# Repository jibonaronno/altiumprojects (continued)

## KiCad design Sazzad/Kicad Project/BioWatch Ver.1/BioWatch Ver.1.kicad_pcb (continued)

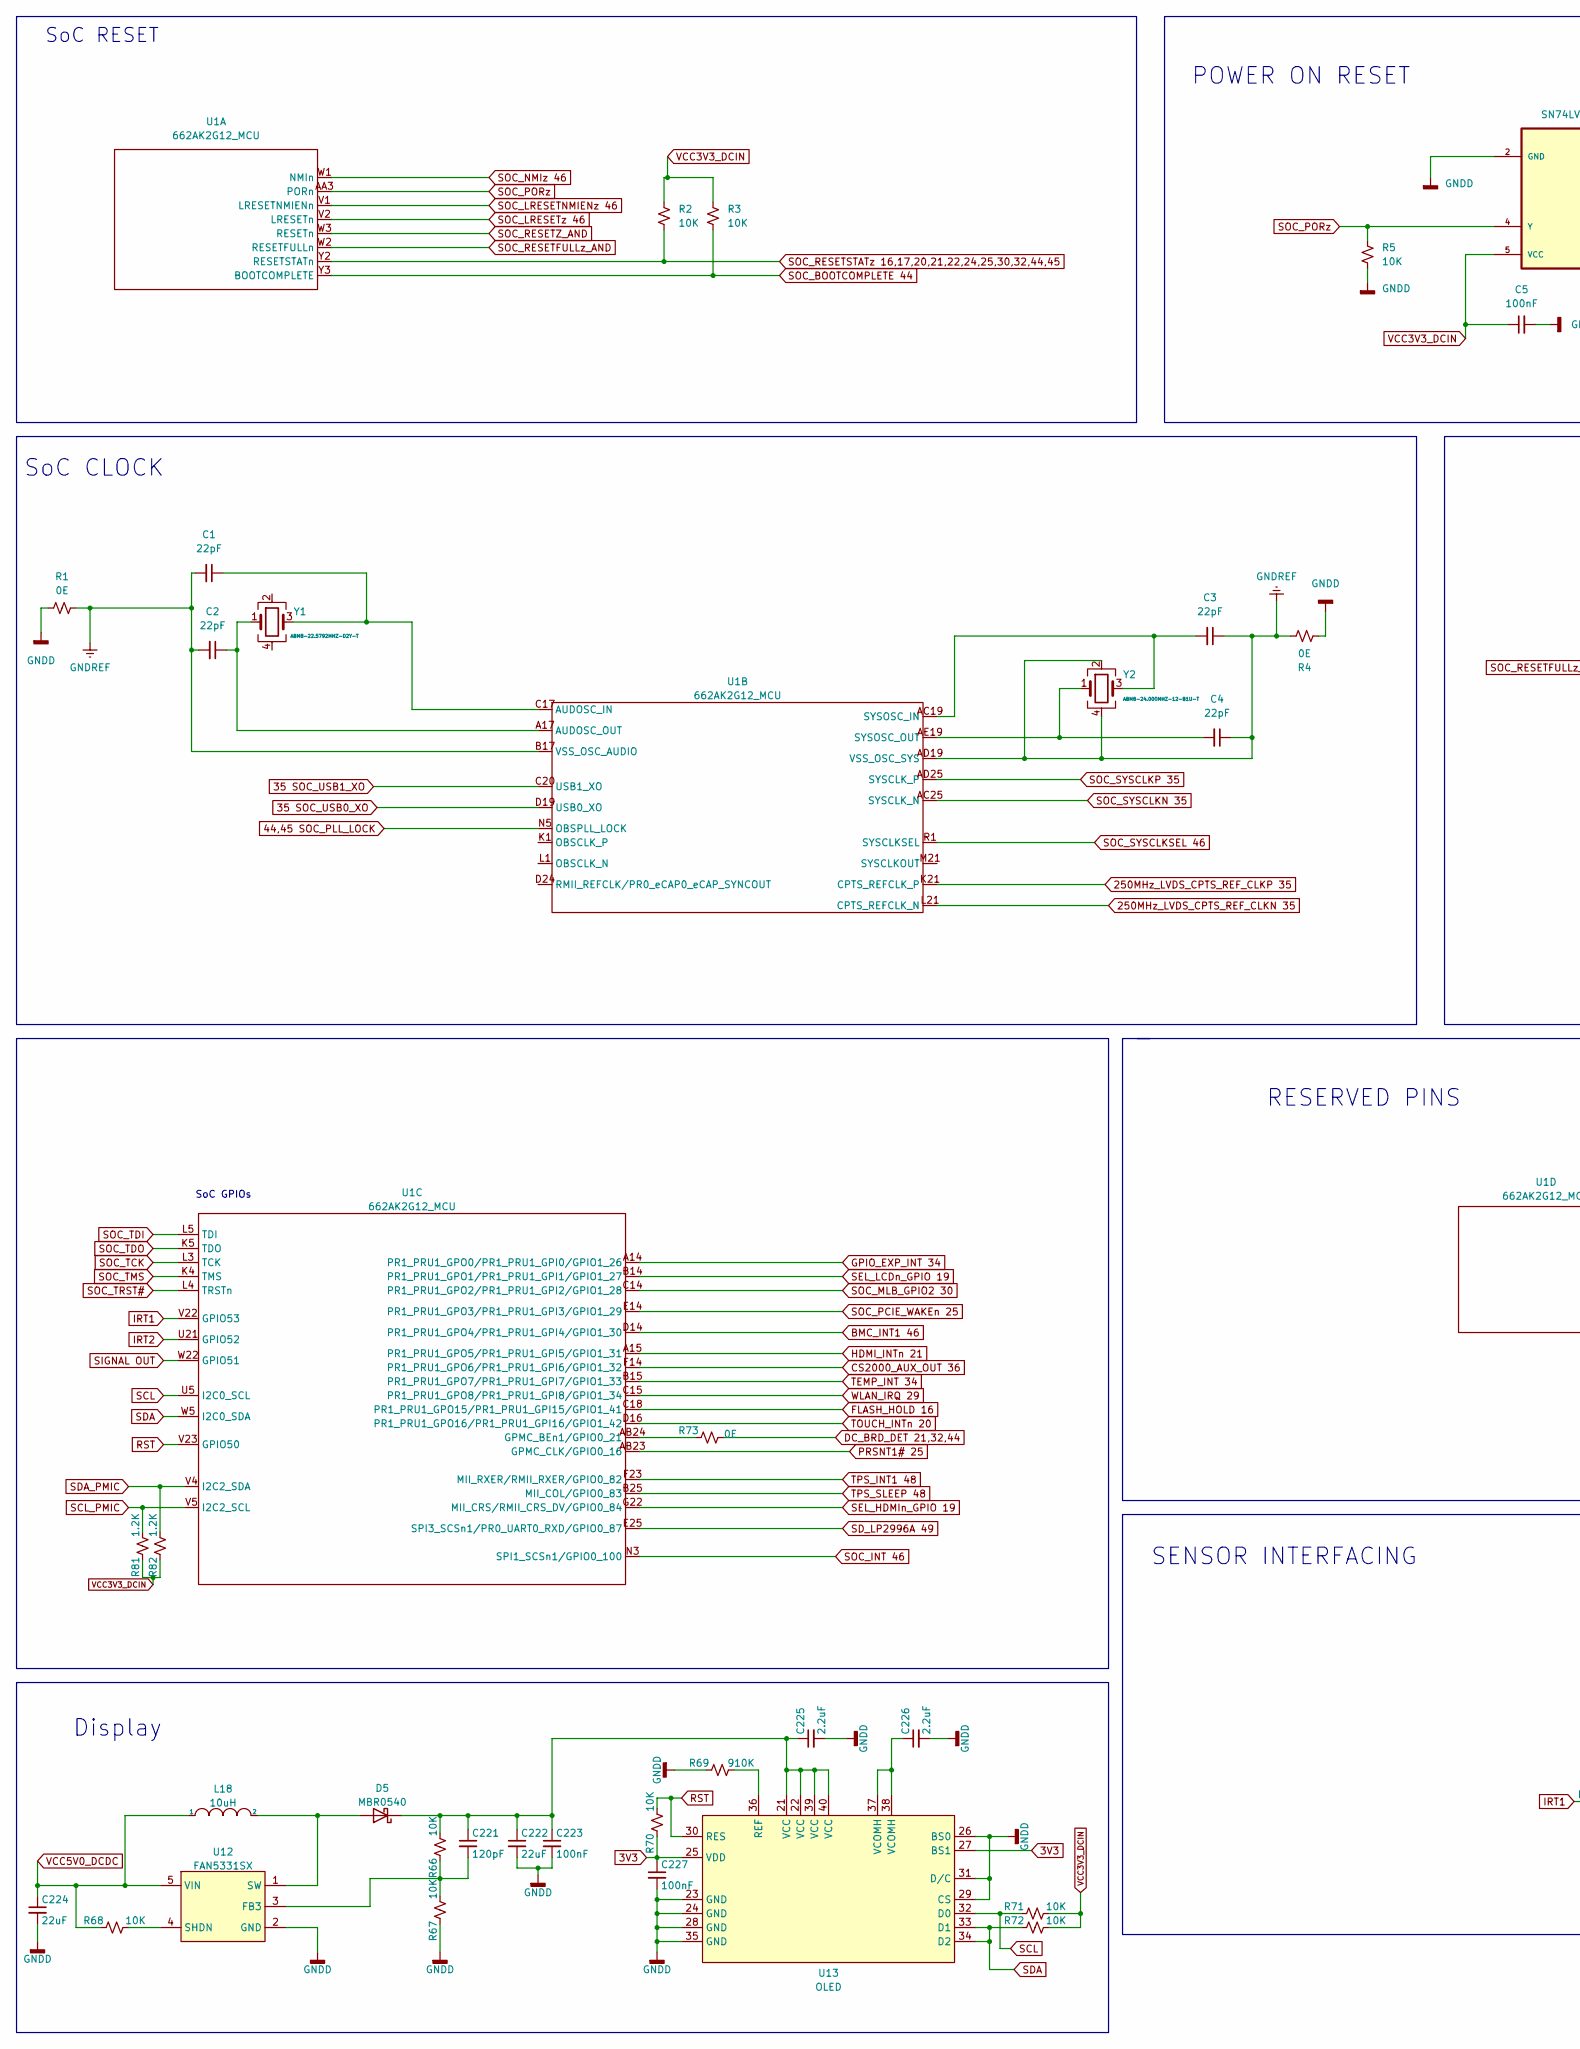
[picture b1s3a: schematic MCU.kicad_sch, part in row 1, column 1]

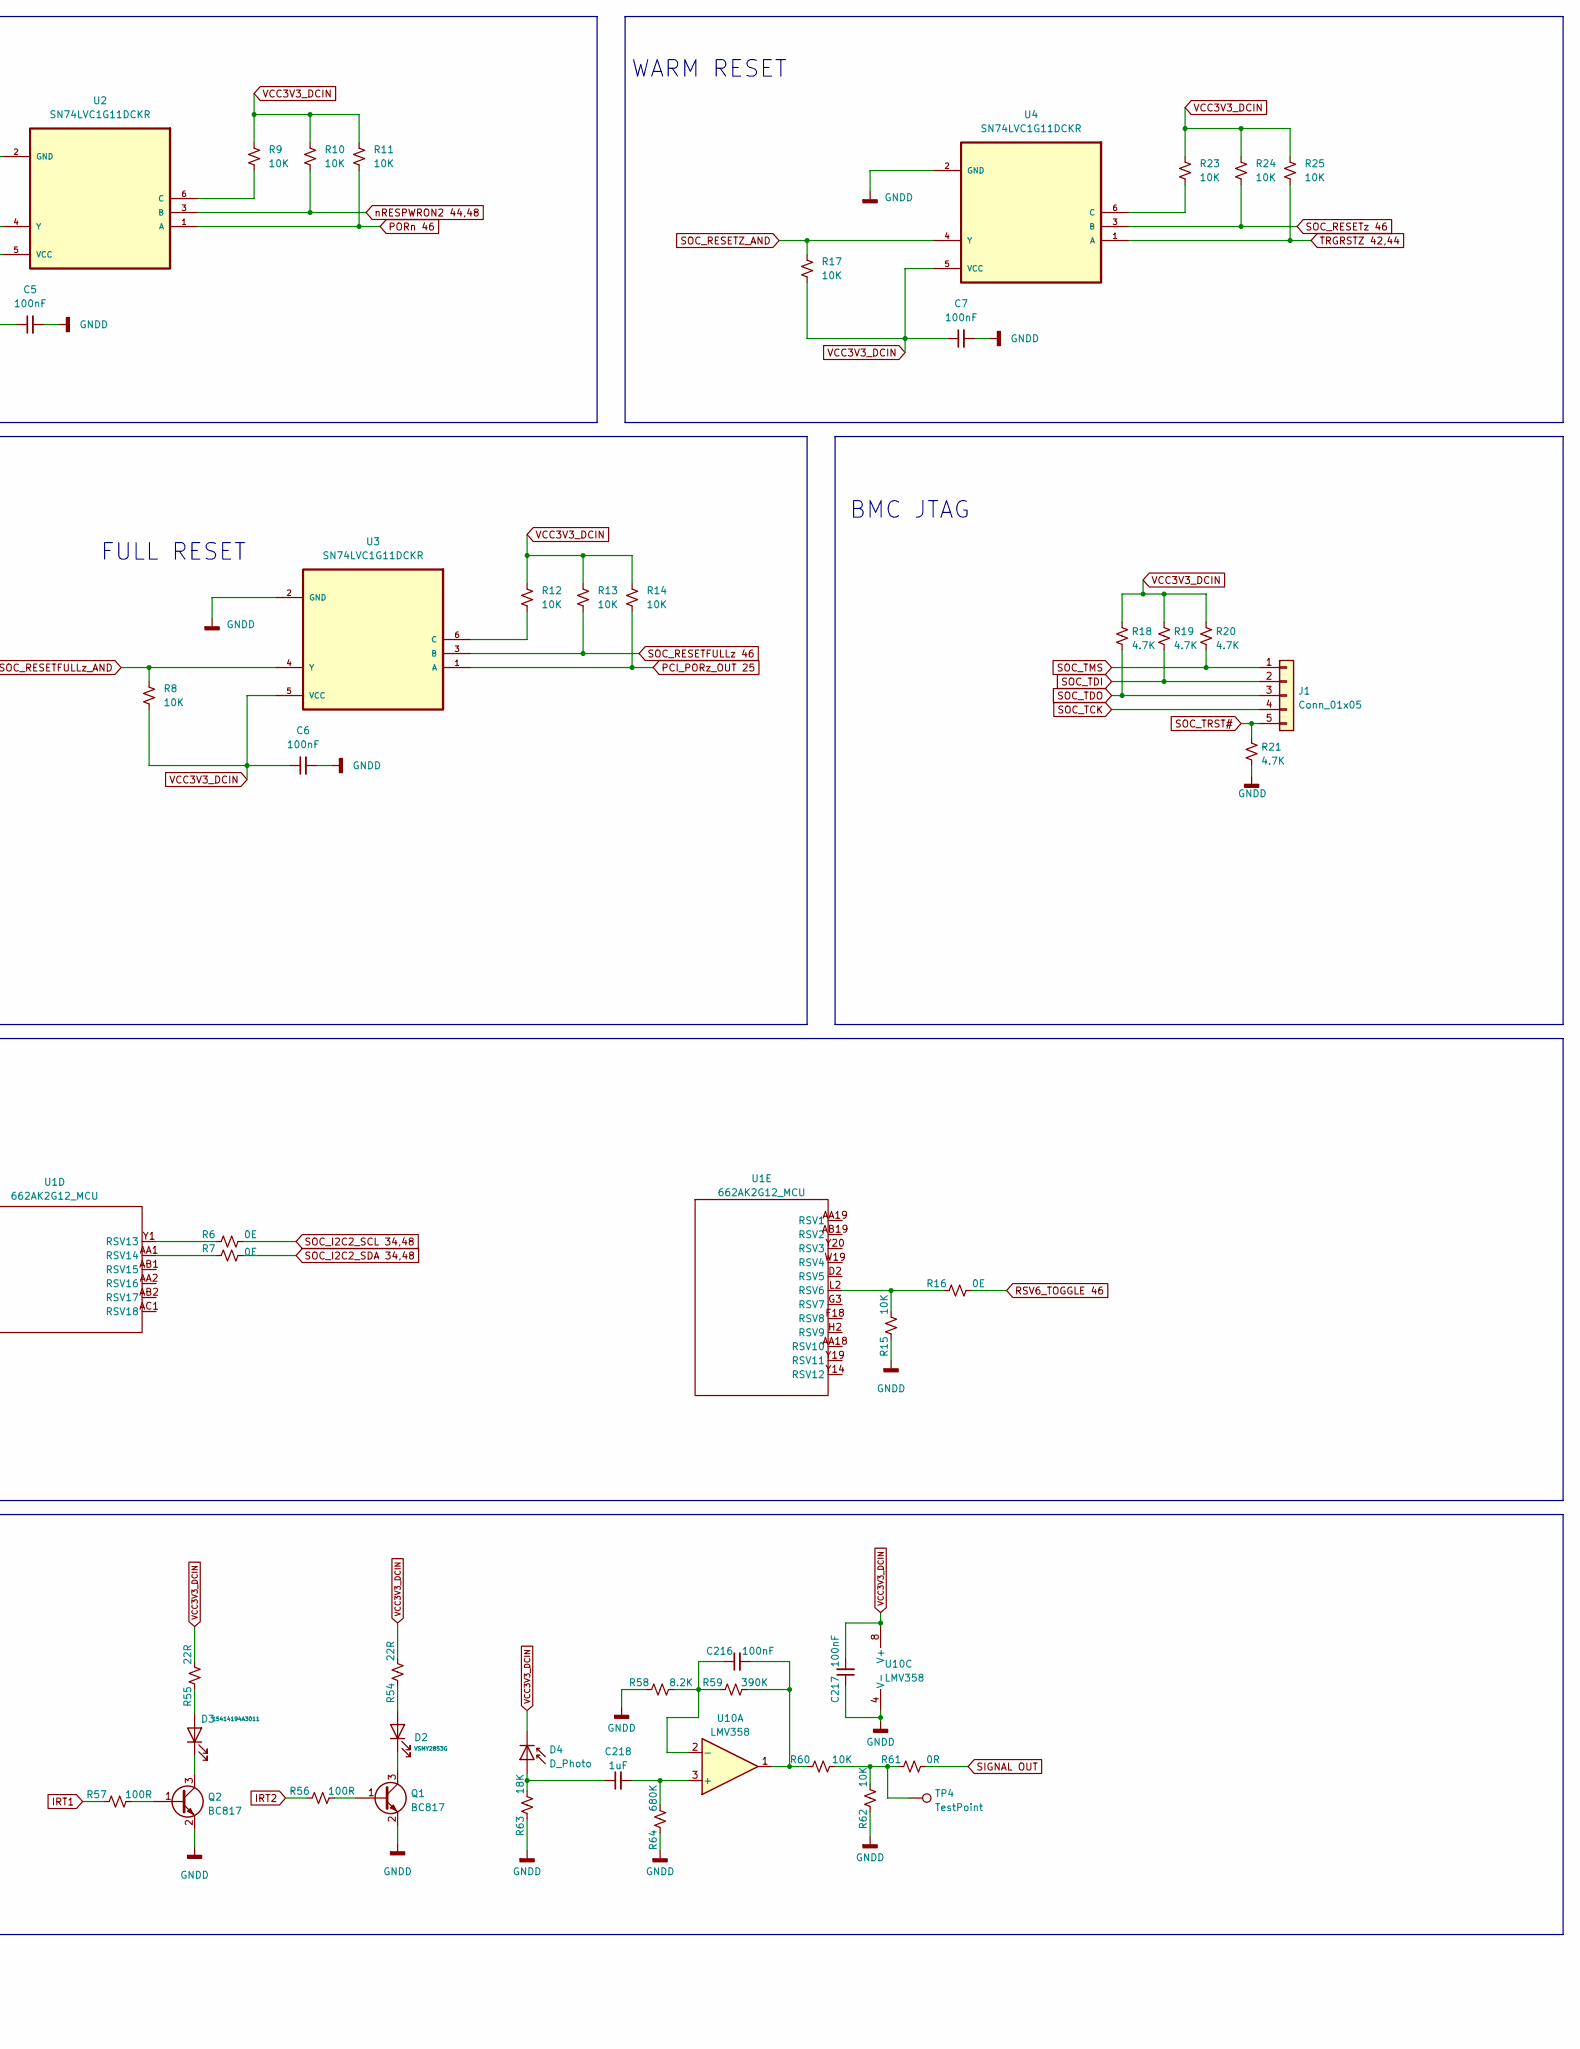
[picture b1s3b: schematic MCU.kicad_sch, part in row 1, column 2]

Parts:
C1, C2, C3, C4: 22pF; C_0402_1005Metric
C5, C6, C7, C216, C217, C223, C227: 100nF; C_0402_1005Metric
C218: 1uF; C_0402_1005Metric
C221: 120pF; C_0402_1005Metric
C222, C224: 22uF; C_0805_2012Metric
C225, C226: 2.2uF; C_0603_1608Metric
D2: VSMY2853G; LED_1812_4532Metric_Pad1.30x3.40mm_HandSolder
D3: 15414194A3011; LED_RGB_Wuerth-PLCC4_3.2x2.8mm_150141M173100
D4: D_Photo; LED_1812_4532Metric_Pad1.30x3.40mm_HandSolder
D5: MBR0540; D_SOD-123
J1: Conn_01x05; PinHeader_1x05_P2.54mm_Vertical
L18: 10uH; L_6.3x6.3_H3
Q1, Q2: BC817; SOT-23
R1, R4: 0E; R_0402_1005Metric
R2, R3, R5, R8, R9, R10, R11, R12, R13, R14, R15, R17, R23, R24, R25, R60, R62, R66, R67, R68, R70, R71, R72: 10K; R_0603_1608Metric
R6, R7, R16, R73: 0E; R_0603_1608Metric
R18, R19, R20, R21: 4.7K; R_0603_1608Metric
R54, R55: 22R; R_0805_2012Metric
R56, R57: 100R; R_0603_1608Metric
R58: 8.2K; R_0603_1608Metric
R59: 390K; R_0603_1608Metric
R61: 0R; R_0603_1608Metric
R63: 18K; R_0603_1608Metric
R64: 680K; R_0603_1608Metric
R69: 910K; R_0603_1608Metric
R81, R82: 1.2K; R_0603_1608Metric
TP4: TestPoint; TestPoint_Pad_D1.0mm
U1: 662AK2G12_MCU; BGA625
U2, U3, U4: SN74LVC1G11DCKR; SOT-23-6_Handsoldering
U10: LMV358; SOIC-8-1EP_3.9x4.9mm_P1.27mm_EP2.29x3mm
U12: FAN5331SX; SOT-23-5_HandSoldering
U13: OLED; PinSocket_2x07_P2.54mm_Vertical
Y1: ABM8-22.5792MHZ-D2Y-T; Crystal_SMD_3225-4Pin_3.2x2.5mm_HandSoldering
Y2: ABM8-24.000MHZ-12-B1U-T; Crystal_SMD_3225-4Pin_3.2x2.5mm_HandSoldering

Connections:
3V3: C227.1, R70.1, U13.25 (VDD), U13.27 (BS1)
35 SOC_USB0_XO: U1.D19 (USB0_XO)
35 SOC_USB1_XO: U1.C20 (USB1_XO)
44,45 SOC_PLL_LOCK: U1.N5 (OBSPLL_LOCK)
250MHz_LVDS_CPTS_REF_CLKN 35: U1.L21 (CPTS_REFCLK_N)
250MHz_LVDS_CPTS_REF_CLKP 35: U1.K21 (CPTS_REFCLK_P)
BMC_INT1 46: U1.D14 (PR1_PRU1_GPO4/PR1_PRU1_GPI4/GPIO1_30)
CS2000_AUX_OUT 36: U1.F14 (PR1_PRU1_GPO6/PR1_PRU1_GPI6/GPIO1_32)
DC_BRD_DET 21,32,44: R73.2
FLASH_HOLD 16: U1.C18 (PR1_PRU1_GPO15/PR1_PRU1_GPI15/GPIO1_41)
GND: C5.2, C6.2, C7.2, C217.1, C222.2, C223.2, C224.2, C225.2, C226.2, C227.2, Q1.2 (E), Q2.2 (E), R1.2, R4.2, R5.2, R15.1, R21.2, R58.1, R62.1, R63.1, R64.1, R67.1, R69.1, U2.2 (GND), U3.2 (GND), U4.2 (GND), U10.4 (V-), U12.2 (GND), U13.23 (GND), U13.24 (GND), U13.26 (BS0), U13.28 (GND), U13.29 (CS), U13.31 (D/C), U13.35 (GND); also elsewhere on the board
GNDREF: C1.2, C2.2, C3.1, C4.1, R1.1, R4.1, U1.AD19 (VSS_OSC_SYS), U1.B17 (VSS_OSC_AUDIO), Y2.2, Y2.4
GPIO_EXP_INT 34: U1.A14 (PR1_PRU1_GPO0/PR1_PRU1_GPI0/GPIO1_26)
HDMI_INTn 21: U1.A15 (PR1_PRU1_GPO5/PR1_PRU1_GPI5/GPIO1_31)
IRT1: R57.1, U1.V22 (GPIO53)
IRT2: R56.1, U1.U21 (GPIO52)
unnamed: C1.1, U1.C17 (AUDOSC_IN), Y1.3
unnamed: C2.1, U1.A17 (AUDOSC_OUT), Y1.1
unnamed: C3.2, U1.AC19 (SYSOSC_IN), Y2.3
unnamed: C4.2, U1.AE19 (SYSOSC_OUT), Y2.1
unnamed: C216.1, R58.2, R59.1, U10.2 (-)
unnamed: C216.2, R59.2, R60.1, U10.1
unnamed: C218.1, D4.2 (A), R63.2
unnamed: C218.2, R64.2, U10.3 (+)
unnamed: C221.1, C222.1, C223.1, C225.1, D5.1 (K), R66.2, U13.21 (VCC), U13.22 (VCC), U13.39 (VCC), U13.40 (VCC)
unnamed: C221.2, R66.1, R67.2, U12.3 (FB3)
unnamed: C226.1, U13.37 (VCOMH), U13.38 (VCOMH)
unnamed: D2.1 (K), Q1.3 (C)
unnamed: D2.2 (A), R54.1
unnamed: D3.1 (K), Q2.3 (C)
unnamed: D3.4 (A), R55.1
unnamed: D5.2 (A), L18.2, U12.1 (SW)
unnamed: Q1.1 (B), R56.2
unnamed: Q2.1 (B), R57.2
unnamed: R6.1, U1.Y1 (RSV13)
unnamed: R7.1, U1.AA1 (RSV14)
unnamed: R9.2, U2.6 (C)
unnamed: R12.2, U3.6 (C)
unnamed: R15.2, R16.1, U1.L2 (RSV6)
unnamed: R23.2, U4.6 (C)
unnamed: R60.2, R61.1, R62.2, TP4.1
unnamed: R68.2, U12.4 (SHDN)
unnamed: R69.2, U13.36 (REF)
unnamed: R73.1, U1.AB24 (GPMC_BEn1/GPIO0_21)
PCI_PORz_OUT 25: R14.2, U3.1 (A)
PORn 46: R11.2, U2.1 (A)
PRSNT1# 25: U1.AB23 (GPMC_CLK/GPIO0_16)
RST: R70.2, U1.V23 (GPIO50), U13.30 (RES)
RSV6_TOGGLE 46: R16.2
SCL: R71.1, U1.U5 (I2C0_SCL), U13.32 (D0)
SCL_PMIC: R81.2, U1.V5 (I2C2_SCL); also elsewhere on the board
SDA: R72.1, U1.W5 (I2C0_SDA), U13.33 (D1), U13.34 (D2)
SDA_PMIC: R82.2, U1.V4 (I2C2_SDA); also elsewhere on the board
SD_LP2996A 49: U1.E25 (SPI3_SCSn1/PR0_UART0_RXD/GPIO0_87)
SEL_HDMIn_GPIO 19: U1.G22 (MII_CRS/RMII_CRS_DV/GPIO0_84)
SEL_LCDn_GPIO 19: U1.B14 (PR1_PRU1_GPO1/PR1_PRU1_GPI1/GPIO1_27)
SIGNAL OUT: R61.2, U1.W22 (GPIO51)
SOC_BOOTCOMPLETE 44: R3.2, U1.Y3 (BOOTCOMPLETE)
SOC_I2C2_SCL 34,48: R6.2
SOC_I2C2_SDA 34,48: R7.2
SOC_INT 46: U1.N3 (SPI1_SCSn1/GPIO0_100)
SOC_LRESETNMIENz 46: U1.V1 (LRESETNMIENn)
SOC_LRESETz 46: U1.V2 (LRESETn)
SOC_MLB_GPIO2 30: U1.C14 (PR1_PRU1_GPO2/PR1_PRU1_GPI2/GPIO1_28)
SOC_NMIz 46: U1.W1 (NMIn)
SOC_PCIE_WAKEn 25: U1.E14 (PR1_PRU1_GPO3/PR1_PRU1_GPI3/GPIO1_29)
SOC_PORz: R5.1, U1.AA3 (PORn), U2.4 (Y)
SOC_RESETFULLz 46: R13.2, U3.3 (B)
SOC_RESETFULLz_AND: R8.1, U1.W2 (RESETFULLn), U3.4 (Y)
SOC_RESETSTATz 16,17,20,21,22,24,25,30,32,44,45: R2.2, U1.Y2 (RESETSTATn)
SOC_RESETZ_AND: R17.1, U1.W3 (RESETn), U4.4 (Y)
SOC_RESETz 46: R24.2, U4.3 (B)
SOC_SYSCLKN 35: U1.AC25 (SYSCLK_N)
SOC_SYSCLKSEL 46: U1.R1 (SYSCLKSEL)
SOC_TCK: J1.4, U1.L3 (TCK)
SOC_TDI: J1.2, R19.2, U1.L5 (TDI)
SOC_TDO: J1.3, R18.2, U1.K5 (TDO)
SOC_TMS: J1.1, R20.2, U1.K4 (TMS)
SOC_TRST#: J1.5, R21.1, U1.L4 (TRSTn)
TEMP_INT 34: U1.B15 (PR1_PRU1_GPO7/PR1_PRU1_GPI7/GPIO1_33)
TOUCH_INTn 20: U1.D16 (PR1_PRU1_GPO16/PR1_PRU1_GPI16/GPIO1_42)
TPS_INT1 48: U1.F23 (MII_RXER/RMII_RXER/GPIO0_82)
TPS_SLEEP 48: U1.B25 (MII_COL/GPIO0_83)
TRGRSTZ 42,44: R25.2, U4.1 (A)
VCC3V3_DCIN: C5.1, C6.1, C7.1, C217.2, D4.1 (K), R2.1, R3.1, R8.2, R9.1, R10.1, R11.1, R12.1, R13.1, R14.1, R17.2, R18.1, R19.1, R20.1, R23.1, R24.1, R25.1, R54.2, R55.2, R71.2, R72.2, R81.1, R82.1, U2.5 (VCC), U3.5 (VCC), U4.5 (VCC), U10.8 (V+); also elsewhere on the board
VCC5V0_DCDC: C224.1, L18.1, R68.1, U12.5 (VIN); also elsewhere on the board
WLAN_IRQ 29: U1.C15 (PR1_PRU1_GPO8/PR1_PRU1_GPI8/GPIO1_34)
nRESPWRON2 44,48: R10.2, U2.3 (B)

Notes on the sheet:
BMC JTAG
RESERVED PINS
POWER ON RESET
SoC RESET
FULL RESET
WARM RESET
SENSOR INTERFACING
SoC GPIOs
Display
SoC CLOCK

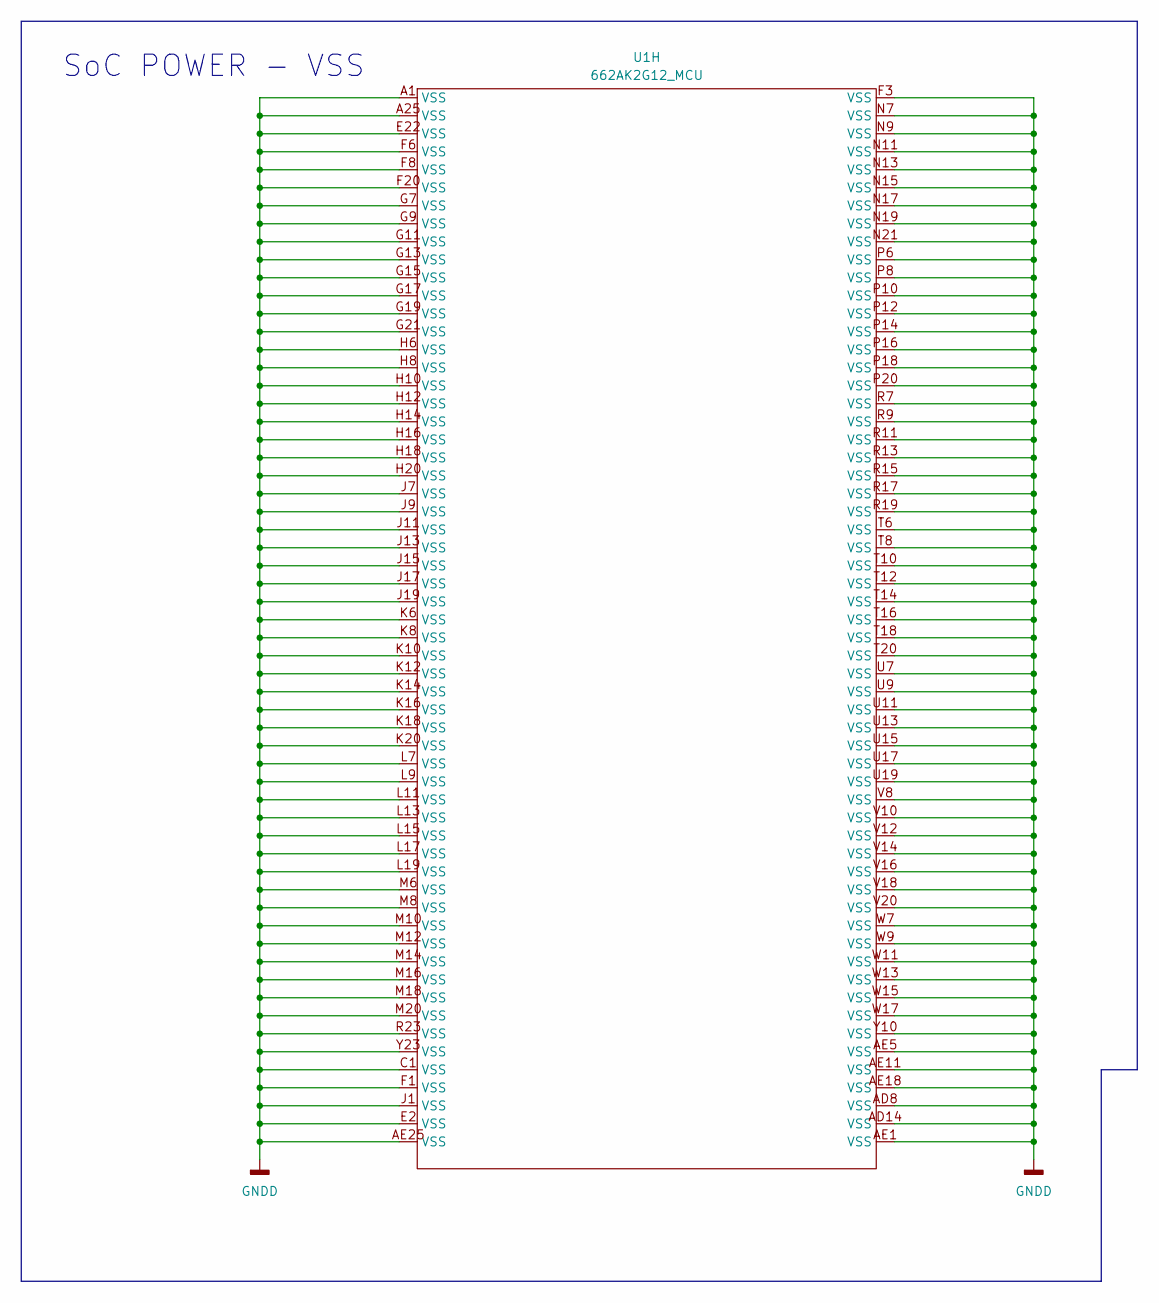
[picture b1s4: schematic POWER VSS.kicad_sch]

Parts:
U1: 662AK2G12_MCU; BGA625

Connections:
GND: U1.A1 (VSS), U1.A25 (VSS), U1.AD8 (VSS), U1.AD14 (VSS), U1.AE1 (VSS), U1.AE5 (VSS), U1.AE11 (VSS), U1.AE18 (VSS), U1.AE25 (VSS), U1.C1 (VSS), U1.E2 (VSS), U1.E22 (VSS), U1.F1 (VSS), U1.F3 (VSS), U1.F6 (VSS), U1.F8 (VSS), U1.F20 (VSS), U1.G7 (VSS), U1.G9 (VSS), U1.G11 (VSS), U1.G13 (VSS), U1.G15 (VSS), U1.G17 (VSS), U1.G19 (VSS), U1.G21 (VSS), U1.H6 (VSS), U1.H8 (VSS), U1.H10 (VSS), U1.H12 (VSS), U1.H14 (VSS), U1.H16 (VSS), U1.H18 (VSS), U1.H20 (VSS), U1.J1 (VSS), U1.J7 (VSS), U1.J9 (VSS), U1.J11 (VSS), U1.J13 (VSS), U1.J15 (VSS), U1.J17 (VSS), U1.J19 (VSS), U1.K6 (VSS), U1.K8 (VSS), U1.K10 (VSS), U1.K12 (VSS), U1.K14 (VSS), U1.K16 (VSS), U1.K18 (VSS), U1.K20 (VSS), U1.L7 (VSS), U1.L9 (VSS), U1.L11 (VSS), U1.L13 (VSS), U1.L15 (VSS), U1.L17 (VSS), U1.L19 (VSS), U1.M6 (VSS), U1.M8 (VSS), U1.M10 (VSS), U1.M12 (VSS), U1.M14 (VSS), U1.M16 (VSS), U1.M18 (VSS), U1.M20 (VSS), U1.N7 (VSS), U1.N9 (VSS), U1.N11 (VSS), U1.N13 (VSS), U1.N15 (VSS), U1.N17 (VSS), U1.N19 (VSS), U1.N21 (VSS), U1.P6 (VSS), U1.P8 (VSS), U1.P10 (VSS), U1.P12 (VSS), U1.P14 (VSS), U1.P16 (VSS), U1.P18 (VSS), U1.P20 (VSS), U1.R7 (VSS), U1.R9 (VSS), U1.R11 (VSS), U1.R13 (VSS), U1.R15 (VSS), U1.R17 (VSS), U1.R19 (VSS), U1.R23 (VSS), U1.T6 (VSS), U1.T8 (VSS), U1.T10 (VSS), U1.T12 (VSS), U1.T14 (VSS), U1.T16 (VSS), U1.T18 (VSS), U1.T20 (VSS), U1.U7 (VSS), U1.U9 (VSS), U1.U11 (VSS), U1.U13 (VSS), U1.U15 (VSS), U1.U17 (VSS), U1.U19 (VSS), U1.V8 (VSS), U1.V10 (VSS), U1.V12 (VSS), U1.V14 (VSS), U1.V16 (VSS), U1.V18 (VSS), U1.V20 (VSS), U1.W7 (VSS), U1.W9 (VSS), U1.W11 (VSS), U1.W13 (VSS), U1.W15 (VSS), U1.W17 (VSS), U1.Y10 (VSS), U1.Y23 (VSS); also elsewhere on the board

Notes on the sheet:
SoC POWER - VSS

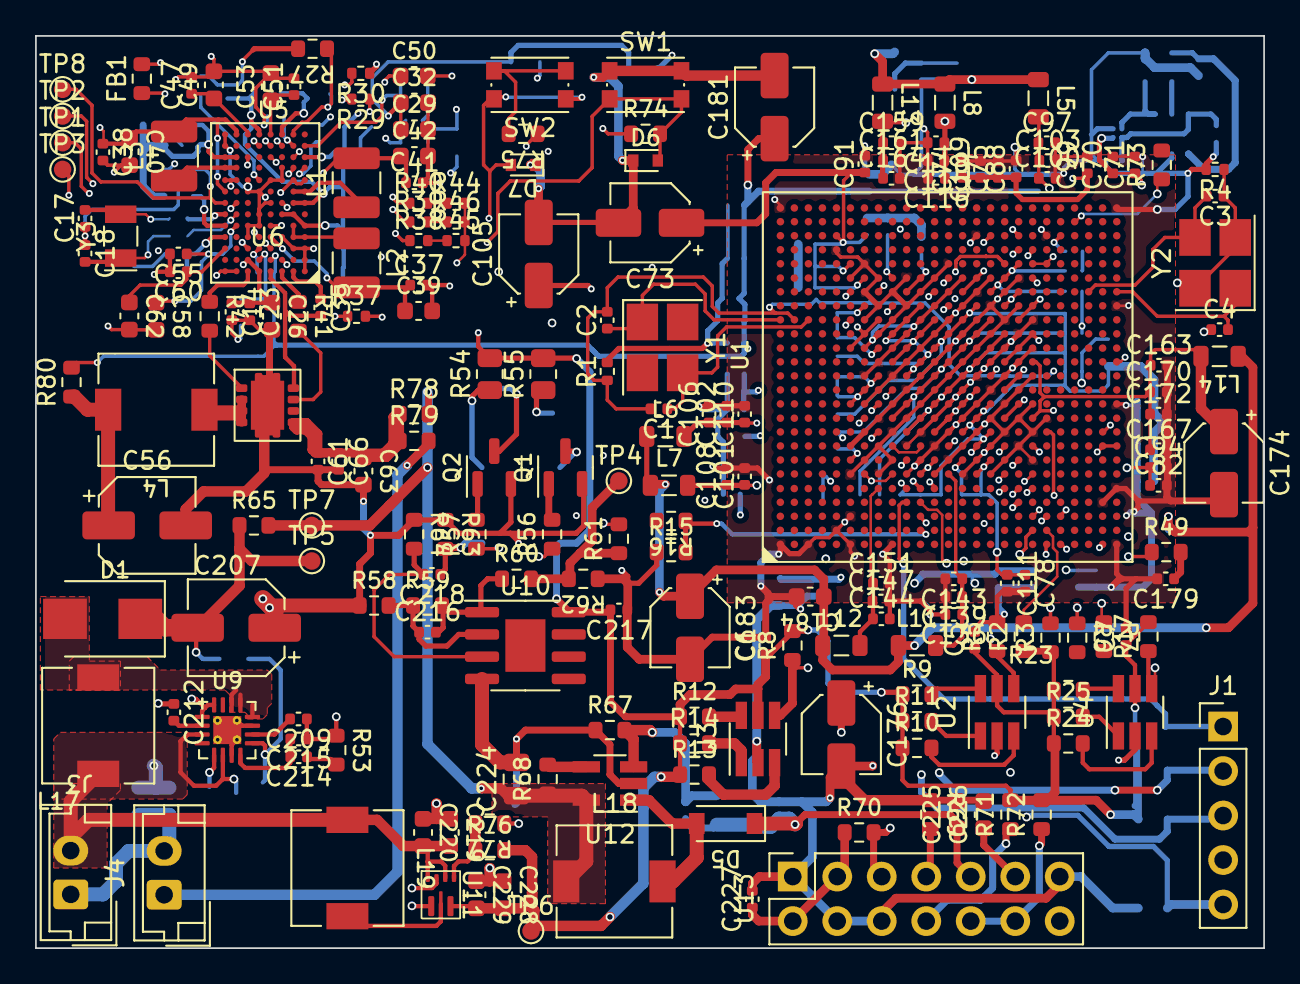
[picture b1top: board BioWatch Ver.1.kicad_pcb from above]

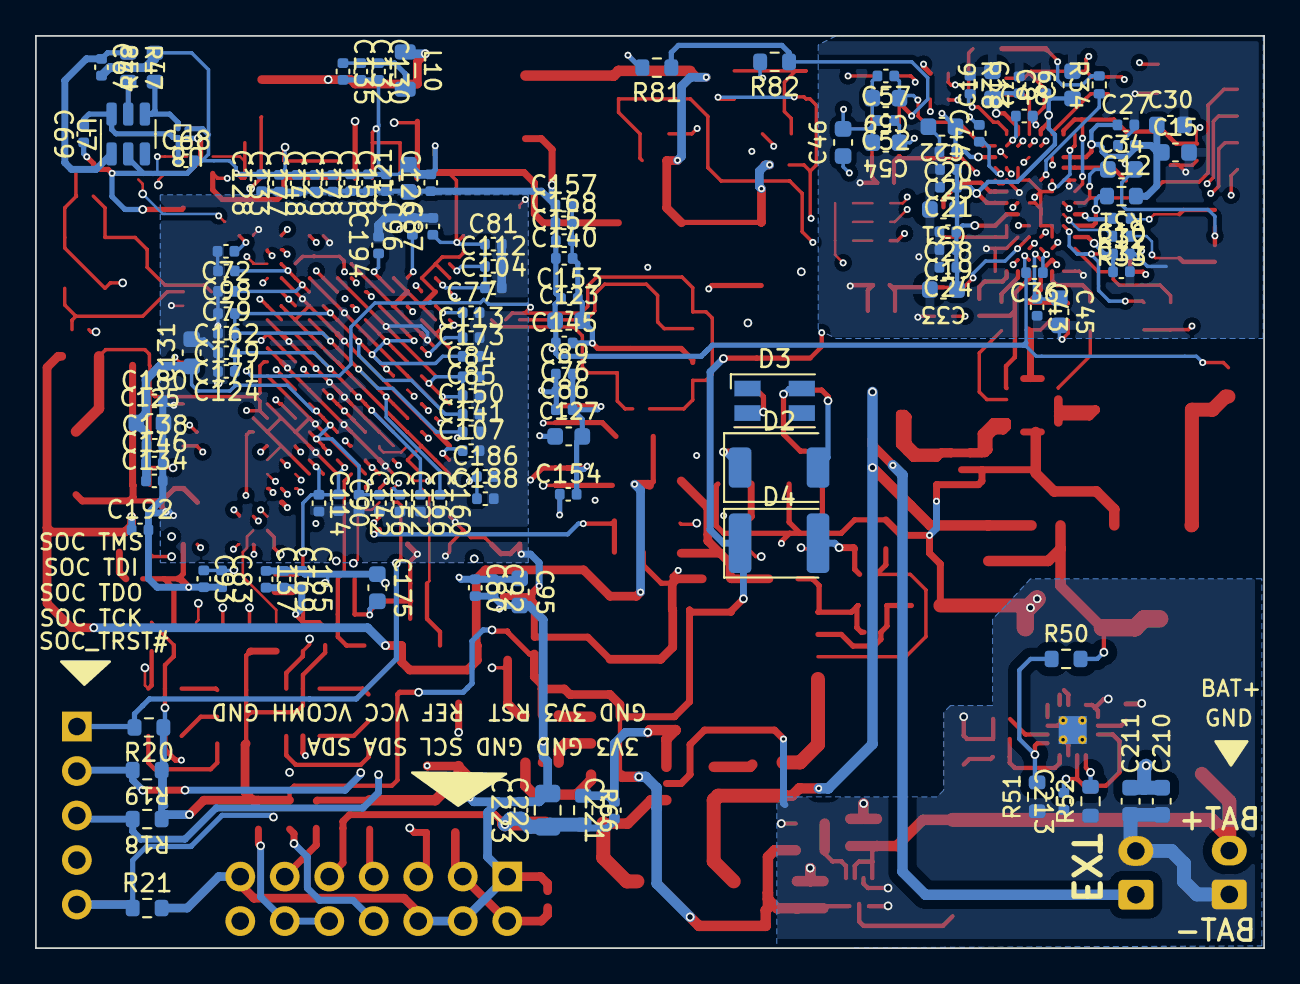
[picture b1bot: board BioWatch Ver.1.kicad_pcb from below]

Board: 4 copper layers, 70.1 x 52.1 mm, 336 parts (133 on the bottom side), 142 nets.

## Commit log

2024-11-01 1-Nov-24
2024-11-04 4-Nov-24
2024-11-05 5-Nov-24
2024-11-05 update from home 6-Nov-2024
2024-11-06 6-Nov-24
2024-11-07 7-Nov-24
2024-11-07 update from home 7-Nov-2024
2024-11-08 8-Nov-24
2024-11-10 update from home 11-Nov-2024
2024-11-11 11-Nov-24
2024-11-11 update from home 12-Nov-2024
2024-11-12 12-Nov-24
2024-11-13 13-Nov-24
2024-11-14 14-Nov-24
2024-11-14 update from home 15-Nov-2024
2024-11-17 update from home 17-Nov-2024
2024-11-18 16-Nov-24
2024-11-19 19-Nov-24
2024-11-19 update from home 18-Nov-2024
2024-11-20 20-Nov-24
2024-11-20 update from home 20-Nov-2024
2024-11-21 21-Nov-24
2024-11-22 22-Nov-24
2024-11-29 29-Nov-24
2025-03-06 QWave CM4 Altium Files added
2025-03-09 2nd part of changes
2025-03-10 Sine wave added to Pyhton PDData Streamer. Generated Sine wave shown in a plot
2025-03-12 12 Mar 2025 Dorm
2025-03-13 14 Mar 2025 Dorm
2025-03-14 14 Mar 25
2025-03-16 17 Mar 2025 Dorm
2025-03-17 17 Mar 25
2025-03-18 18 Mar 25
2025-03-19 19 Mar 25
2025-03-19 19 Mar 2025 Dorm
2025-03-20 20 Mar 25
2025-03-21 21 Mar 25
2025-03-23 23 Mar 2025 Dorm
2025-04-11 11 Apr 25
2025-04-13 13 April 2025 Dorm
2025-04-14 14 Apr 25
2025-04-14 14 April 2025 Dorm
2025-04-15 15 Apr 25
2025-05-15 15 May 25
2025-05-15 15 May 2025 Dorm
2025-05-16 16 May 25
2025-05-19 20 May 2025 Dorm
2025-05-20 20 May 25
2025-05-21 21 May 25
2025-05-24 24 May 25
2025-05-25 25 May 2025 Dorm
2025-05-26 26 May 25
2025-05-27 27 May 25
2025-05-28 28 May 2025 Dorm
2025-05-29 28 May 25
2025-06-01 1 June 2025 Dorm
2025-06-03 3 June 2025 Dorm
2025-06-09 9 June 2025 Dorm
2025-06-10 10 JUN 25 Office
2025-06-10 10 June 2025 Dorm
2025-06-11 11 JUN 25 Office
2025-06-11 11 June 2025 Dorm
2025-06-12 12 May 25 Office
2025-06-13 13 May 25 Office
2025-06-13 13 June 2025 Dorm
2025-06-15 15 June 2025 Dorm
2025-06-16 16 June 25 Office
2025-06-17 17 June 25 Office
2025-06-18 18 June 25 Office
2025-06-19 18 June 2025 Dorm
2025-06-20 20 June 2025 Dorm
2025-06-20 USB-C Port placed like a small single board
2025-06-22 21 June 2025 Dorm
2025-06-23 23 June 2025 Dorm
2025-06-24 24 June 25 Office
2025-06-24 24 June 2025 Dorm
2025-06-25 25 June 25 Office
2025-06-25 25 June 2025 Dorm
2025-06-26 26 June 2025 Dorm
2025-06-28 28 June 2025 Dorm
2025-06-30 30 June 2025 Dorm
2025-07-01 0.2 July 25 Office
2025-07-01 1 July 2025 Dorm
2025-07-02 2.3 July 25 Office
2025-07-02 2 July 2025 Dorm
2025-07-03 3 July 25 Office
2025-07-06 06 July 2025 Dorm
2025-07-11 11 july 2025 office
2025-07-11 12 July 2025 Dorm
2025-07-13 13 July 2025 Dorm
2025-07-13 14 July 2025 Dorm
2025-07-14 14 July 25 Office
2025-07-15 15 july 2025 office
2025-07-15 15.0 July 25 Office
2025-07-15 15.02 july 2025 office
2025-07-15 15 July 2025 Dorm
2025-07-16 16 july 2025 office
2025-07-16 16 July 2025 Dorm
2025-07-17 17 july 2025 office
2025-07-20 21 July 2025 Dorm
2025-07-21 21 july 2025 office
2025-07-23 22 july 2025 office
2025-07-24 24 july 2025 office
2025-07-27 27 July 2025 Dorm
2025-07-28 28 july 2025 office
2025-07-30 31 August 2025 Dorm
2025-07-31 1 Aug 2025 Dorm
2025-08-01 2 Aug 2025 Dorm
2025-08-03 3 Aug 2025 Dorm
2025-08-04 5 Aug 2025 Dorm
2025-08-06 6 Aug 2025 Dorm
2025-08-06 6 Aug 2025 Dorm 2
2025-08-06 6 Aug 2025 Dorm 3
2025-08-07 7 Aug 2025 Dorm 1
2025-08-07 8 Aug 2025 Dorm 1
2025-08-08 8 Aug 2025 Dorm 2
2025-08-08 8 Aug 2025 Dorm 3
2025-08-09 9 Aug 2025 Dorm 1
2025-08-10 10 Aug 2025 Dorm 1
2025-08-10 10 Aug 2025 Dorm 2
2025-08-16 16 Aug 2025 Dorm 1
2025-08-18 18 Aug 2025 Dorm 1
2025-08-19 19 Aug 2025 Dorm 1
2025-08-25 25 Aug 2025 Dorm 1
2025-08-25 25 Aug 2025 Starbucks
2025-08-29 29 Aug 2025 Home With Support Lines
2025-09-03 3 Sept Home
2025-09-15 16 Sept Home
